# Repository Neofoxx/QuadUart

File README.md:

# QuadUart
A Quad UART to USB converter, based on PIC32.

## Overview

This project uses a PIC32MX564F128H micro to implement a quad UART-USB converter. The idea is to use an open-source toolchain to create a useful project, and one can **never** have too many UART converters

At least 4x 115200bps is supported, with plans to go to 4x 1Mbps, speed of the micro permitting.

Exposed pins are TX, RX, and DTR.

## Toolchain

The entire toolchain is open source:
- MCU definitions from the [SpicaStack](https://gitlab.com/spicastack/pic32-parts-free) project
- Compiler is GCC for mipsel crosscompiling. A ready-to-go package can be found [here](https://build.opensuse.org/package/show/home:neofoxx/gcc-mipsel-elf) (Ubuntu, Fedora, OpenSuse packges currently built)
- The USB stack is [M-stack](https://github.com/signal11/m-stack)
- PCB is provided as a set of Gerber files, and as a KiCAD project.

## TODO

- Add fiducails to PCB
- Add pinout to Readme
- License

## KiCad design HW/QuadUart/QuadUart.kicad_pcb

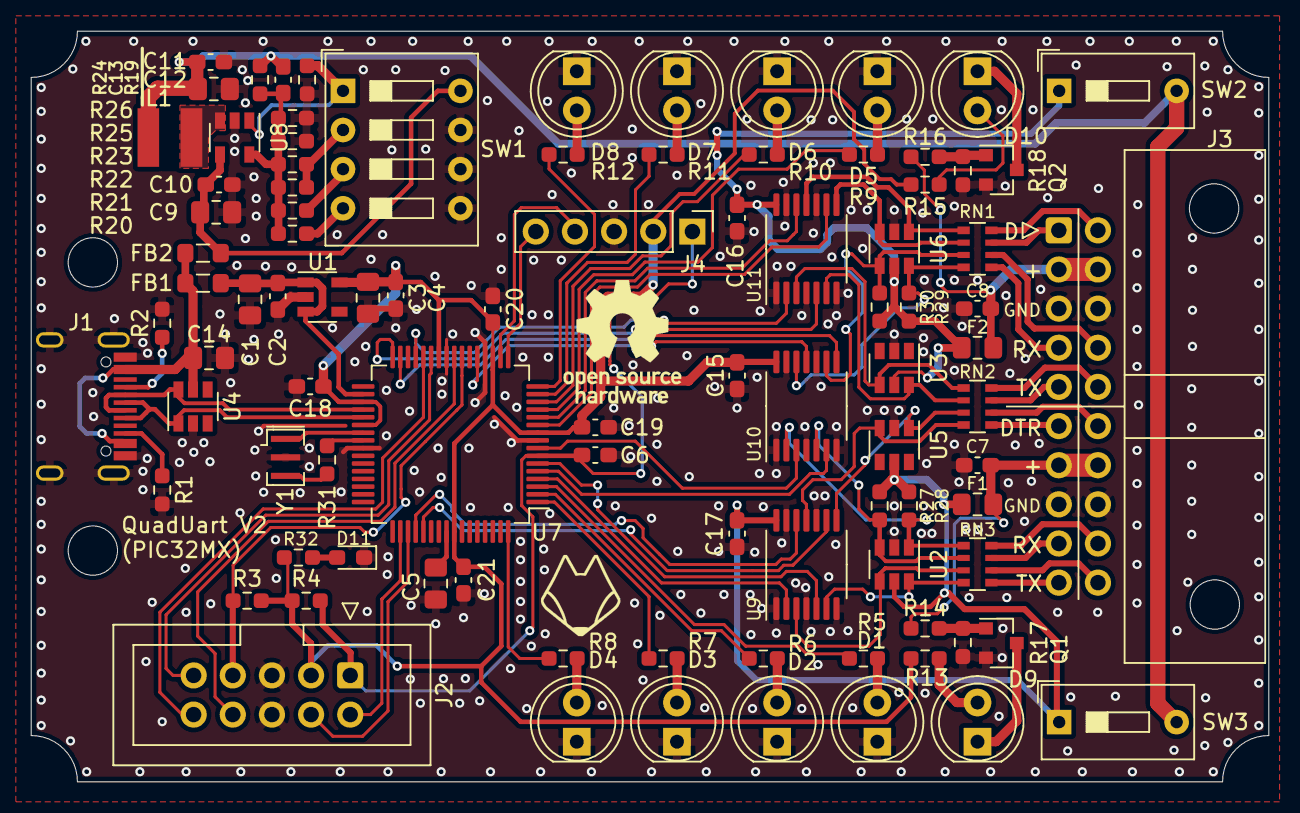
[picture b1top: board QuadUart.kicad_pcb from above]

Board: 2 copper layers, 80.3 x 48.7 mm, 100 parts (1 on the bottom side), 92 nets.

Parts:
C1, C3, C9, C12: 4.7uF; C_0805_2012Metric_Pad1.18x1.45mm_HandSolder
C2, C4, C6, C7, C8, C10, C11, C15, C16, C17, C18, C19, C20, C21: 100nF; C_0603_1608Metric_Pad1.08x0.95mm_HandSolder
C5, C14: 10uF; C_0805_2012Metric_Pad1.18x1.45mm_HandSolder
C13: DNS; C_0603_1608Metric_Pad1.08x0.95mm_HandSolder
D1, D2, D3, D4, D5, D6, D7, D8, D9, D10: LED; LED_D5.0mm
D11: LED; LED_0603_1608Metric_Pad1.05x0.95mm_HandSolder
F1, F2: Polyfuse; Fuse_0805_2012Metric_Pad1.15x1.40mm_HandSolder
FB1, FB2: Ferrite_Bead_Small; L_0805_2012Metric_Pad1.05x1.20mm_HandSolder
H1, H2, H3, H4: MountingHole; MountingHole_3.2mm_M3
J1: USB_C_Receptacle_USB2.0; Jing USB C 2.0 16pin receptable
J2: Conn_02x05_Odd_Even; IDC-Header_2x05_P2.54mm_Vertical
J3: Conn_02x10_Odd_Even; IDC-Header_2x10_P2.54mm_Horizontal
J4: Conn_01x05; PinHeader_1x05_P2.54mm_Vertical
L1: 1.5uH; SMNR4018_(1616FPS)
LOGO1: Logo_Open_Hardware_Small; OSHW-Logo_7.5x8mm_SilkScreen
MARK1: LOGO; FOX_LOGO_MASK
MARK2: LOGO; FOX_LOGO_SILK
Q1, Q2: BC847; SOT-23
R1, R2: 5.1k; R_0603_1608Metric_Pad0.98x0.95mm_HandSolder
R3, R4, R19: 100k; R_0603_1608Metric_Pad0.98x0.95mm_HandSolder
R5, R6, R7, R8, R9, R10, R11, R12, R13, R15, R32: R; R_0603_1608Metric_Pad0.98x0.95mm_HandSolder
R14, R16, R17, R18: 10k; R_0603_1608Metric_Pad0.98x0.95mm_HandSolder
R20: 27k; R_0603_1608Metric_Pad0.98x0.95mm_HandSolder
R21: 180k; R_0603_1608Metric_Pad0.98x0.95mm_HandSolder
R22: 470k; R_0603_1608Metric_Pad0.98x0.95mm_HandSolder
R23: 330k; R_0603_1608Metric_Pad0.98x0.95mm_HandSolder
R24, R25, R26, R27, R28, R29, R30: 220k; R_0603_1608Metric_Pad0.98x0.95mm_HandSolder
R31: 0R; R_0603_1608Metric_Pad0.98x0.95mm_HandSolder
RN1, RN2, RN3: R_Pack04; R_Array_Convex_4x0603
SW1: SW_DIP_x04; SW_DIP_SPSTx04_Slide_9.78x12.34mm_W7.62mm_P2.54mm
SW2, SW3: SW_DIP_x01; SW_DIP_SPSTx01_Slide_9.78x4.72mm_W7.62mm_P2.54mm
U1: LN1134-3.3V; SOT-23-5
U2, U3, U4, U5, U6: SRV05-4; SOT-23-6
U7: PIC32MX564F128H; TQFP-64_10x10mm_P0.5mm
U8: BL8028; SOT-23-5
U9, U10, U11: SN74LV4T125; TSSOP-14_4.4x5mm_P0.65mm
Y1: Crystal_GND2; Resonator_SMD_muRata_CSTxExxV-3Pin_3.0x1.1mm

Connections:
+3V3: C3.1, C4.1, C15.1, C18.1, C19.1, C20.1, C21.1, J2.3, J4.2, R3.2, R4.2, R13.2, R15.2, R32.2, U1.5, U7.10, U7.19, U7.26, U7.35, U7.38, U7.57, U10.14
+5V: C1.1, C2.1, FB1.1, U1.1, U1.3, U7.34
/D+: J1.A6, J1.B6, U4.1, U7.37
/D-: J1.A7, J1.B7, U4.6, U7.36
/DTR_1: J3.11, RN2.5
/DTR_1_RES: RN2.4, U5.3, U9.11
/DTR_1_UC: U7.52, U9.12
/DTR_2: J3.12, RN2.6
/DTR_2_RES: RN2.3, U5.1, U9.8
/DTR_2_UC: U7.53, U9.9
/DTR_3: J3.1, RN1.7
/DTR_3_RES: RN1.2, U6.3, U11.8
/DTR_3_UC: U7.11, U11.9
/DTR_4: J3.2, RN1.8
/DTR_4_RES: RN1.1, U6.1, U11.11
/DTR_4_UC: U7.12, U11.12
/EN_1: R19.1, SW1.1, U8.1
/FB_1: C13.2, R20.1, R21.1, R22.1, R23.1, R24.2, R25.1, R26.1, U8.5
/LED_RX_1: R6.2, U7.2
/LED_RX_2: R8.2, U7.64
/LED_RX_3: R10.2, U7.14
/LED_RX_4: R12.2, U7.16
/LED_TX_1: R5.2, U7.3
/LED_TX_2: R7.2, U7.1
/LED_TX_3: R9.2, U7.13
/LED_TX_4: R11.2, U7.15
/OSC1: U7.39, Y1.1
/OSC2: R31.2, U7.40
/PGEC2: J4.5, U7.17
/PGED2: J4.4, U7.18
/PWR_1: C7.1, F1.1, J3.13, J3.14, R14.2
/PWR_2: C8.1, F2.1, J3.3, J3.4, R16.2
/RX_1: J3.17, RN3.7
/RX_1_RES: R27.2, RN3.2, U2.3, U10.5
/RX_1_UC: U7.5, U10.6
/RX_2: J3.18, RN3.8
/RX_2_RES: R28.2, RN3.1, U2.1, U10.2
/RX_2_UC: U7.8, U10.3
/RX_3: J3.7, RN1.5
/RX_3_RES: R29.2, RN1.4, U6.6, U10.12
/RX_3_UC: U7.31, U10.11
/RX_4: J3.8, RN1.6
/RX_4_RES: R30.2, RN1.3, U6.4, U10.9
/RX_4_UC: U7.21, U10.8
/RX_DBG: J2.2, U7.50
/SW_1_2.5V: R22.2, R23.2, SW1.2
/SW_1_3.3V: R21.2, SW1.3
/SW_1_5.0V: R20.2, SW1.4
/TCK: J2.9, U7.27
/TDI: J2.10, U7.28
/TDO: J2.8, U7.24
/TMS: J2.7, R3.1, U7.23
/TX_1: J3.19, RN3.5
/TX_1_RES: RN3.4, U2.6, U9.6
/TX_1_UC: U7.6, U9.5
/TX_2: J3.20, RN3.6
/TX_2_RES: RN3.3, U2.4, U9.3
/TX_2_UC: U7.4, U9.2
/TX_3: J3.9, RN2.7
/TX_3_RES: RN2.2, U3.6, U11.6
/TX_3_UC: U7.32, U11.5
/TX_4: J3.10, RN2.8
/TX_4_RES: RN2.1, U3.4, U11.3
/TX_4_UC: U7.29, U11.2
/TX_DBG: J2.4, U7.51
/VBUS: C14.1, FB1.2, FB2.2, J1.A4, U4.5
/VBUS_DCDC_5V: C9.1, C10.1, FB2.1, SW1.8, U8.4
/VCAP: C5.1, U7.56
/~MCLR~: C6.1, J2.1, J4.1, R4.1, U7.7
GND: C1.2, C2.2, C3.2, C4.2, C5.2, C6.2, C7.2, C8.2, C9.2, C10.2, C11.2, C12.2, C14.2, C15.2, C16.2, C17.2, C18.2, C19.2, C20.2, C21.2, D1.1, D2.1, D3.1, D4.1, D5.1, D6.1, D7.1, D8.1, D11.1, J1.A1, J1.S1, J2.5, J2.6, J3.5, J3.6, J3.15, J3.16, J4.3, Q1.2, Q2.2, R1.2, R2.2, R17.1, R18.1, R19.2, R25.2, R26.2, SW1.5, SW1.6, SW1.7, U1.2, U2.2, U3.2, U4.2, U5.2, U6.2, U7.9, U7.20, U7.25, U7.41, U8.2, U9.1, U9.4, U9.7, U9.10, U9.13, U10.1, U10.4, U10.7, U10.10, U10.13, U11.1, U11.4, U11.7, U11.10, U11.13, Y1.2
unnamed: C11.1, C12.1, C13.1, L1.2, R24.1, SW2.2, SW3.2
unnamed: D1.2, R5.1
unnamed: D2.2, R6.1
unnamed: D3.2, R7.1
unnamed: D4.2, R8.1
unnamed: D5.2, R9.1
unnamed: D6.2, R10.1
unnamed: D7.2, R11.1
unnamed: D8.2, R12.1
unnamed: D9.1, Q1.3
unnamed: D9.2, R13.1
unnamed: D10.1, Q2.3
unnamed: D10.2, R15.1
unnamed: D11.2, R32.1
unnamed: J1.A5, R2.1
unnamed: J1.B5, R1.1
unnamed: L1.1, U8.3
unnamed: Q1.1, R14.1, R17.2
unnamed: Q2.1, R16.1, R18.2
unnamed: R31.1, Y1.3
VCC: C17.1, F1.2, R27.1, R28.1, SW3.1, U2.5, U5.5, U9.14
VDD: C16.1, F2.2, R29.1, R30.1, SW2.1, U3.5, U6.5, U11.14

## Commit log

2020-11-28 Mid-work commit. Dimensions and placement done
2020-11-29 Finished layout, added Gerbers
2020-12-06 Added 2 capacitors (ESD) and changed fuse position.
2020-12-06 Modified silkscreen. Exported gerbers
2020-12-06 On close change
2020-12-20 Fixed Input/output swap on buffers, increased to V2
2020-12-20 Update README, add LICENSE file, add whatever was from autosave of PCB
2021-01-03 First SW commit. Compiles and shows 2 UARTS for now
2021-01-06 Mid-work commit
2021-01-07 Mid-work commit. Now shows up as 4 devices
2021-01-10 First version of multiple UARTs working, loopback test OK, has some issues with opening/closing
2021-01-10 Fix copy&paste error
